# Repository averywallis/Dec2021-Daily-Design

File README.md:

# Dec2021-Daily-Design
 Advent of PCBs 2021

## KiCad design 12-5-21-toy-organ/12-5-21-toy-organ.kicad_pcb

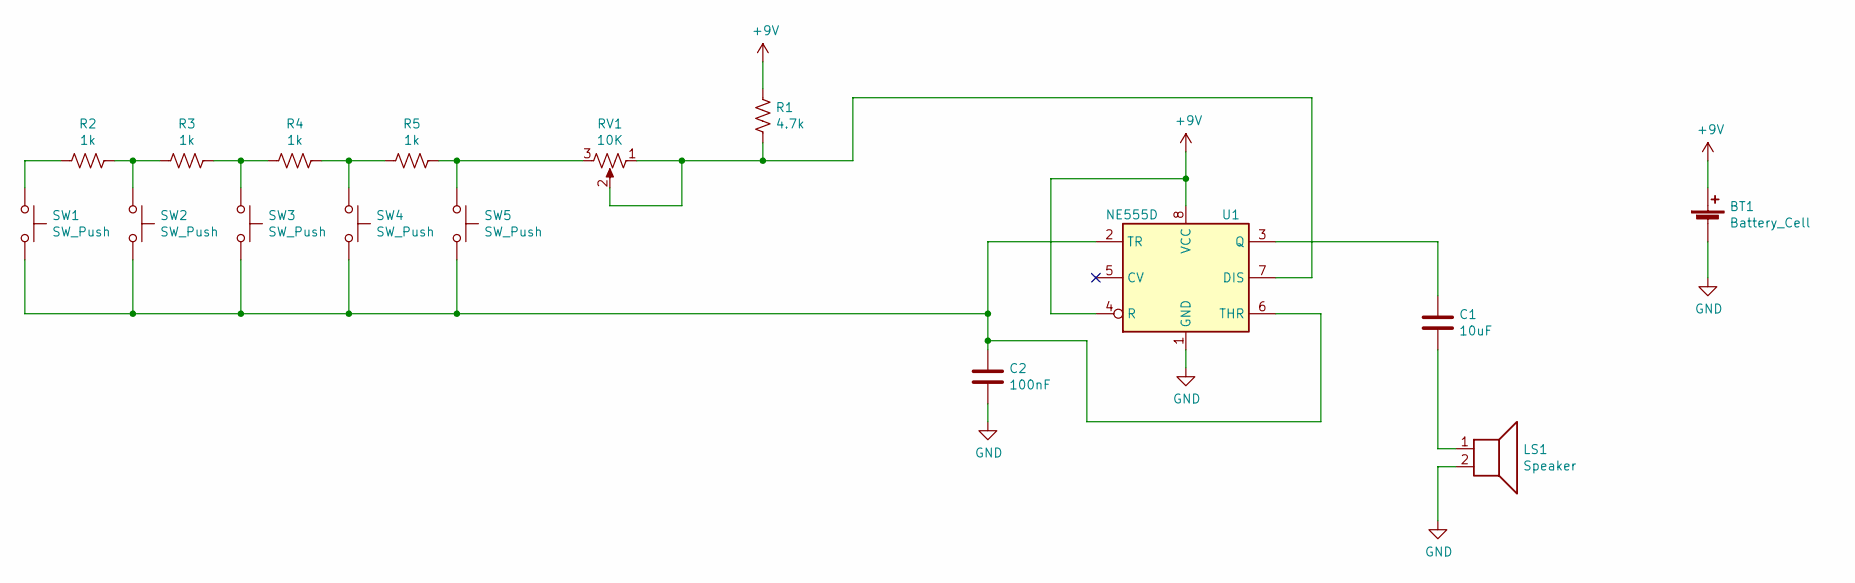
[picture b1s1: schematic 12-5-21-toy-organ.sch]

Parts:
BT1: Battery_Cell; BatteryHolder_Eagle_12BH611-GR
C1: 10uF; C_0805_2012Metric_Pad1.18x1.45mm_HandSolder
C2: 100nF; C_0805_2012Metric_Pad1.18x1.45mm_HandSolder
LS1: Speaker; PinHeader_1x02_P2.54mm_Vertical
R1: 4.7k; R_0805_2012Metric_Pad1.20x1.40mm_HandSolder
R2, R3, R4, R5: 1k; R_0805_2012Metric_Pad1.20x1.40mm_HandSolder
RV1: 10K; Potentiometer_Bourns_3299W_Vertical
SW1, SW2, SW3, SW4, SW5: SW_Push; SW_SPST_CK_RS282G05A3
U1: NE555D; SOIC-8_3.9x4.9mm_P1.27mm

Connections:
+9V: BT1.1 (+), R1.2, U1.4 (R), U1.8 (VCC)
GND: BT1.2 (-), C2.2, LS1.2, U1.1 (GND)
unnamed: C1.1, U1.3 (Q)
unnamed: C1.2, LS1.1
unnamed: C2.1, SW1.2, SW2.2, SW3.2, SW4.2, SW5.2, U1.2 (TR), U1.6 (THR)
unnamed: R1.1, RV1.1, RV1.2, U1.7 (DIS)
unnamed: R2.1, SW1.1
unnamed: R2.2, R3.1, SW2.1
unnamed: R3.2, R4.1, SW3.1
unnamed: R4.2, R5.1, SW4.1
unnamed: R5.2, RV1.3, SW5.1

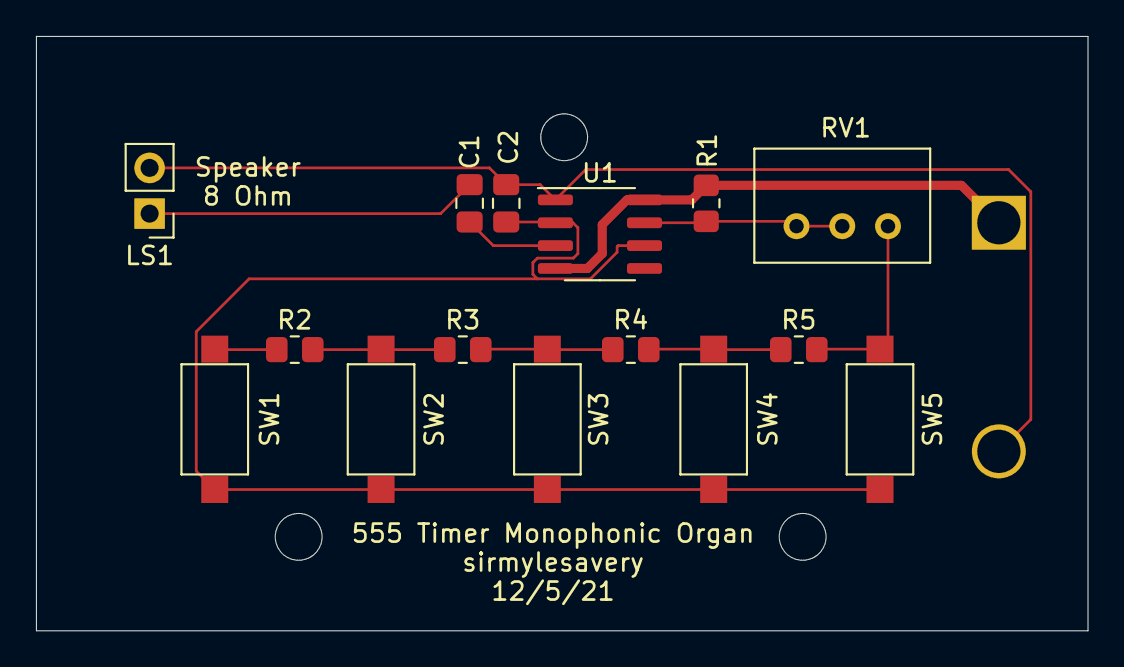
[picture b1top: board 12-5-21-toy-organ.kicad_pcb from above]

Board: 2 copper layers, 58.4 x 33.0 mm, 16 parts (1 on the bottom side), 11 nets.

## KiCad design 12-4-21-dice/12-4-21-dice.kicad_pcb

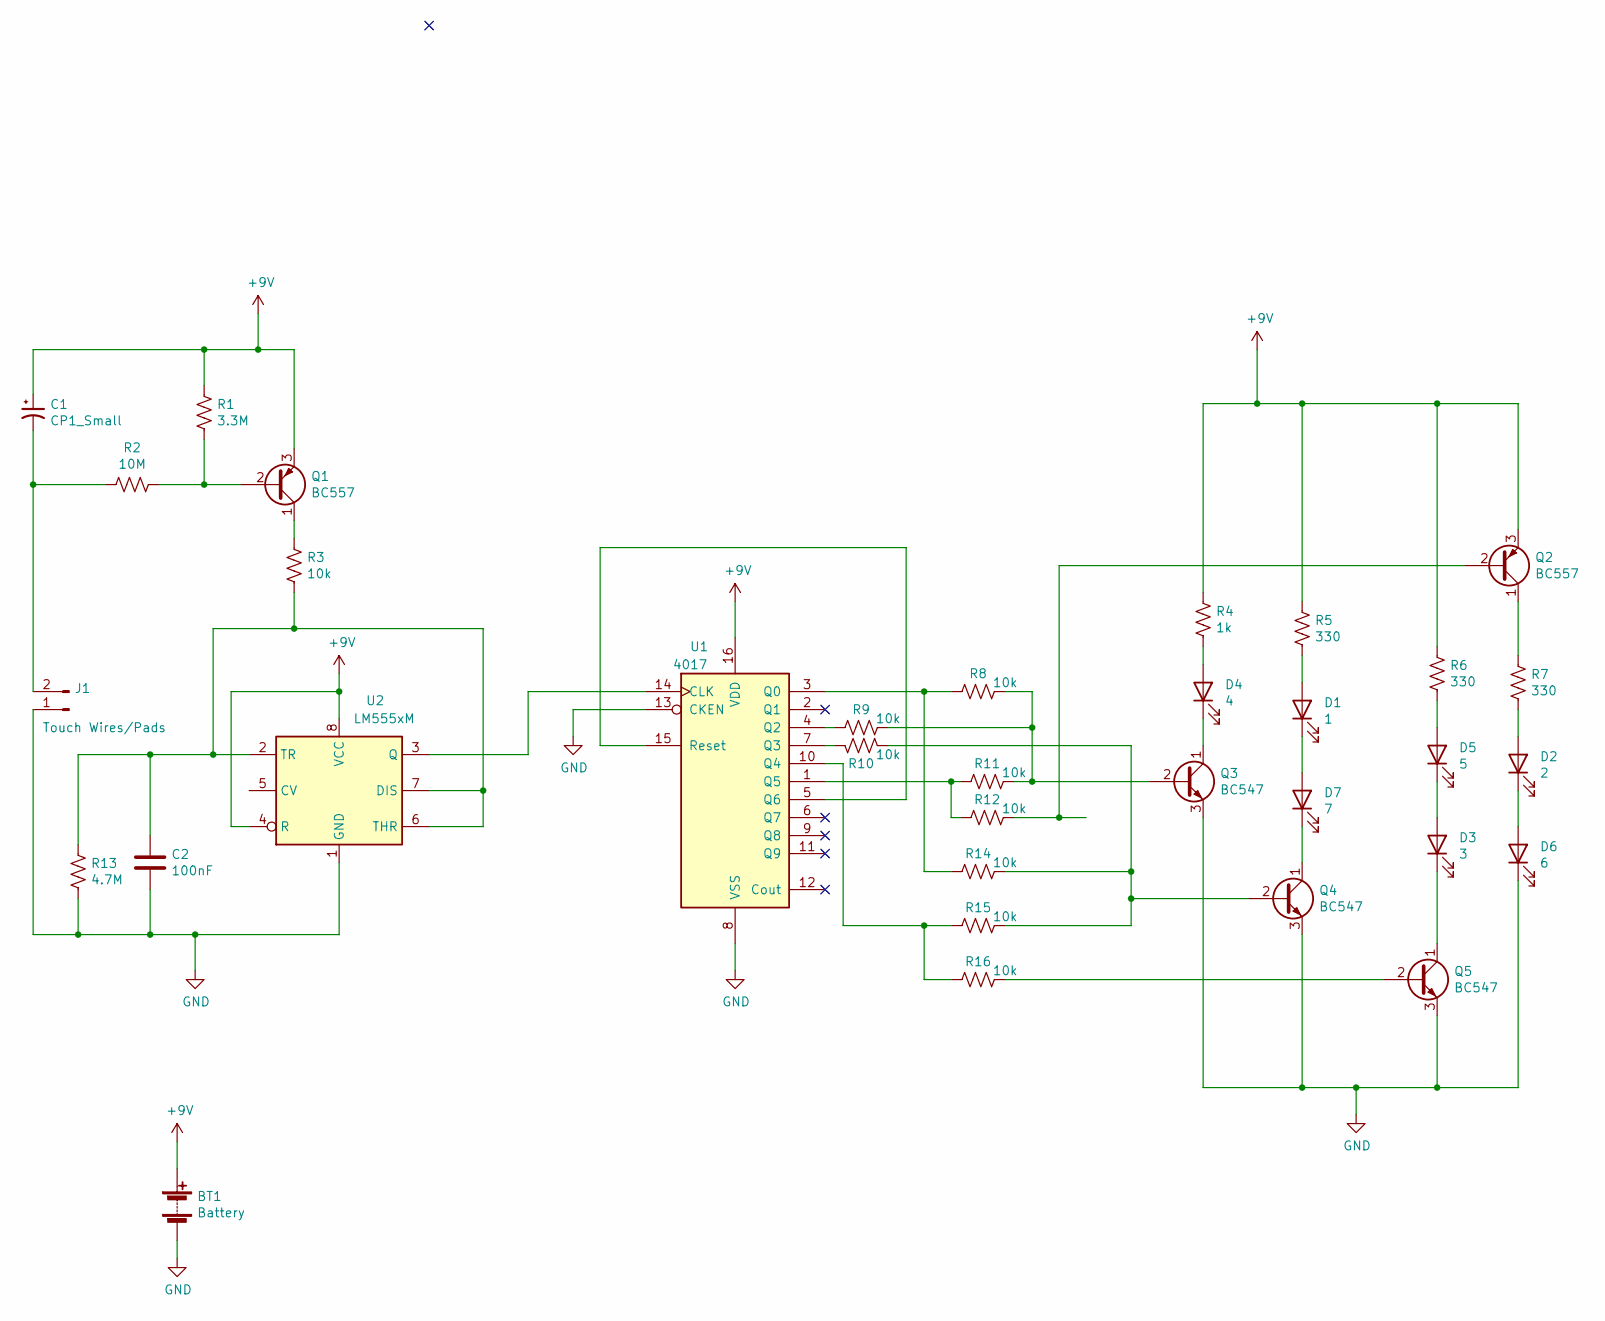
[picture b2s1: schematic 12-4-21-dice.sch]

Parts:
BT1: Battery; BatteryHolder_Eagle_12BH611-GR
C1: CP1_Small; CP_Radial_D5.0mm_P2.50mm
C2: 100nF; C_0805_2012Metric_Pad1.18x1.45mm_HandSolder
D1: 1; LED_0805_2012Metric_Pad1.15x1.40mm_HandSolder
D2: 2; LED_0805_2012Metric_Pad1.15x1.40mm_HandSolder
D3: 3; LED_0805_2012Metric_Pad1.15x1.40mm_HandSolder
D4: 4; LED_0805_2012Metric_Pad1.15x1.40mm_HandSolder
D5: 5; LED_0805_2012Metric_Pad1.15x1.40mm_HandSolder
D6: 6; LED_0805_2012Metric_Pad1.15x1.40mm_HandSolder
D7: 7; LED_0805_2012Metric_Pad1.15x1.40mm_HandSolder
J1: Touch Wires/Pads; C_3640_9110Metric_Pad2.10x10.45mm_HandSolder
Q1, Q2: BC557; TO-92_Inline
Q3, Q4, Q5: BC547; TO-92_Inline
R1: 3.3M; R_0805_2012Metric_Pad1.20x1.40mm_HandSolder
R2: 10M; R_0805_2012Metric_Pad1.20x1.40mm_HandSolder
R3, R8, R9, R10, R11, R12, R14, R15, R16: 10k; R_0805_2012Metric_Pad1.20x1.40mm_HandSolder
R4: 1k; R_0805_2012Metric_Pad1.20x1.40mm_HandSolder
R5, R6, R7: 330; R_0805_2012Metric_Pad1.20x1.40mm_HandSolder
R13: 4.7M; R_0805_2012Metric_Pad1.20x1.40mm_HandSolder
U1: 4017; DIP-16_W10.16mm
U2: LM555xM; SOIC-8_3.9x4.9mm_P1.27mm

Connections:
+9V: BT1.1 (+), C1.1, Q1.3 (E), Q2.3 (E), R1.1, R4.1, R5.1, R6.1, U1.16 (VDD), U2.4 (R), U2.8 (VCC)
GND: BT1.2 (-), C2.2, D6.1 (K), J1.1, Q3.3 (E), Q4.3 (E), Q5.3 (E), R13.2, U1.8 (VSS), U1.13 (CKEN), U2.1 (GND)
unnamed: C1.2, J1.2, R2.2
unnamed: C2.1, R3.2, R13.1, U2.2 (TR), U2.6 (THR), U2.7 (DIS)
unnamed: D1.1 (K), D7.2 (A)
unnamed: D1.2 (A), R5.2
unnamed: D2.1 (K), D6.2 (A)
unnamed: D2.2 (A), R7.2
unnamed: D3.1 (K), Q5.1 (C)
unnamed: D3.2 (A), D5.1 (K)
unnamed: D4.1 (K), Q3.1 (C)
unnamed: D4.2 (A), R4.2
unnamed: D5.2 (A), R6.2
unnamed: D7.1 (K), Q4.1 (C)
unnamed: Q1.1 (C), R3.1
unnamed: Q1.2 (B), R1.2, R2.1
unnamed: Q2.1 (C), R7.1
unnamed: Q2.2 (B), R12.1
unnamed: Q3.2 (B), R8.1, R9.1, R11.1
unnamed: Q4.2 (B), R10.1, R14.1, R15.1
unnamed: Q5.2 (B), R16.1
unnamed: R9.2, U1.4 (Q2)
unnamed: R10.2, U1.7 (Q3)
unnamed: R11.2, R12.2, U1.1 (Q5)
unnamed: R8.2, R14.2, U1.3 (Q0)
unnamed: R15.2, R16.2, U1.10 (Q4)
unnamed: U1.14 (CLK), U2.3 (Q)
unnamed: U1.5 (Q6), U1.15 (Reset)

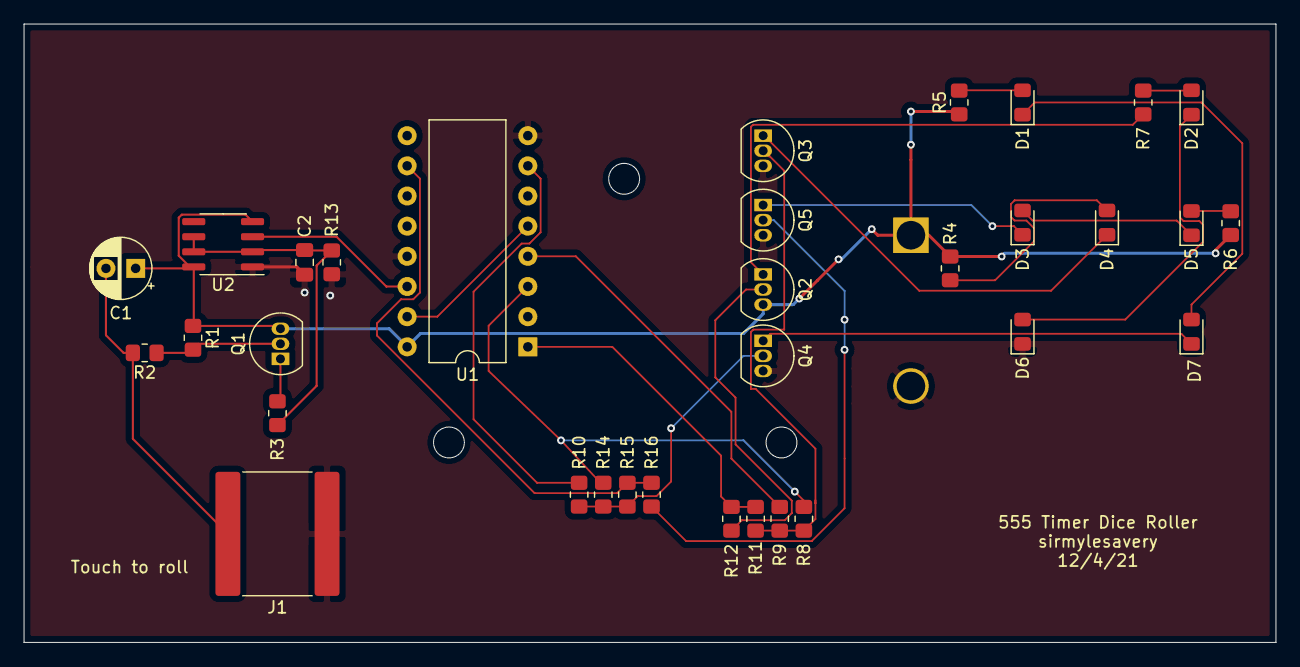
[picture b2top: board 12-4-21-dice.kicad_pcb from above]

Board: 2 copper layers, 105.4 x 52.1 mm, 34 parts (1 on the bottom side), 28 nets.

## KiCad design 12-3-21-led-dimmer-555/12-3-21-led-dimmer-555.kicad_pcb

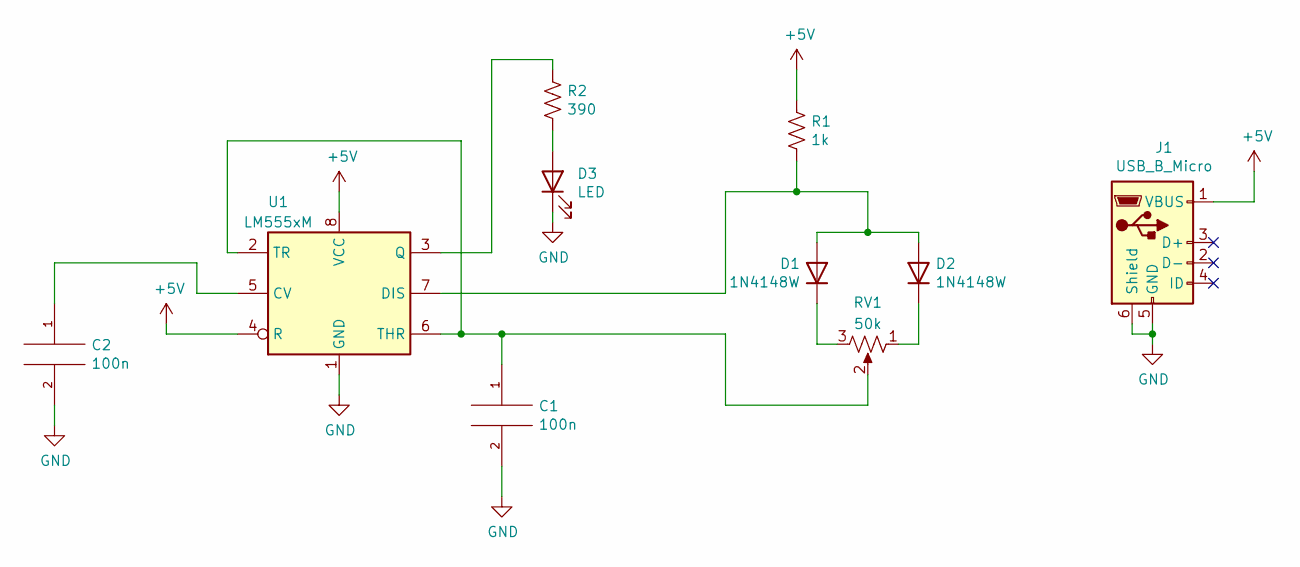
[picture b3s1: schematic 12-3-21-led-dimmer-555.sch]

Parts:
C1, C2: 100n; C_0603_1608Metric
D1, D2: 1N4148W; D_SOD-123
D3: LED; LED_0603_1608Metric
J1: USB_B_Micro; USB_Micro-B_Amphenol_10103594-0001LF_Horizontal
R1: 1k; R_0603_1608Metric
R2: 390; R_0603_1608Metric
RV1: 50k; Potentiometer_Bourns_3224G_Horizontal
U1: LM555xM; SOIC-8_3.9x4.9mm_P1.27mm

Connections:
+5V: J1.1 (VBUS), R1.1, U1.4 (R), U1.8 (VCC)
GND: C1.2, C2.2, D3.1 (K), J1.5 (GND), J1.6 (Shield), U1.1 (GND)
unnamed: C1.1, RV1.2, U1.2 (TR), U1.6 (THR)
unnamed: C2.1, U1.5 (CV)
unnamed: D1.1 (K), RV1.3
unnamed: D1.2 (A), D2.2 (A), R1.2, U1.7 (DIS)
unnamed: D2.1 (K), RV1.1
unnamed: D3.2 (A), R2.2
unnamed: R2.1, U1.3 (Q)

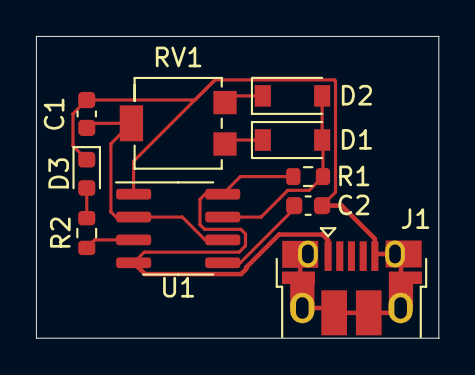
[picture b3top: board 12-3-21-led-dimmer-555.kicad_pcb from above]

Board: 2 copper layers, 22.4 x 16.8 mm, 10 parts (0 on the bottom side), 9 nets.

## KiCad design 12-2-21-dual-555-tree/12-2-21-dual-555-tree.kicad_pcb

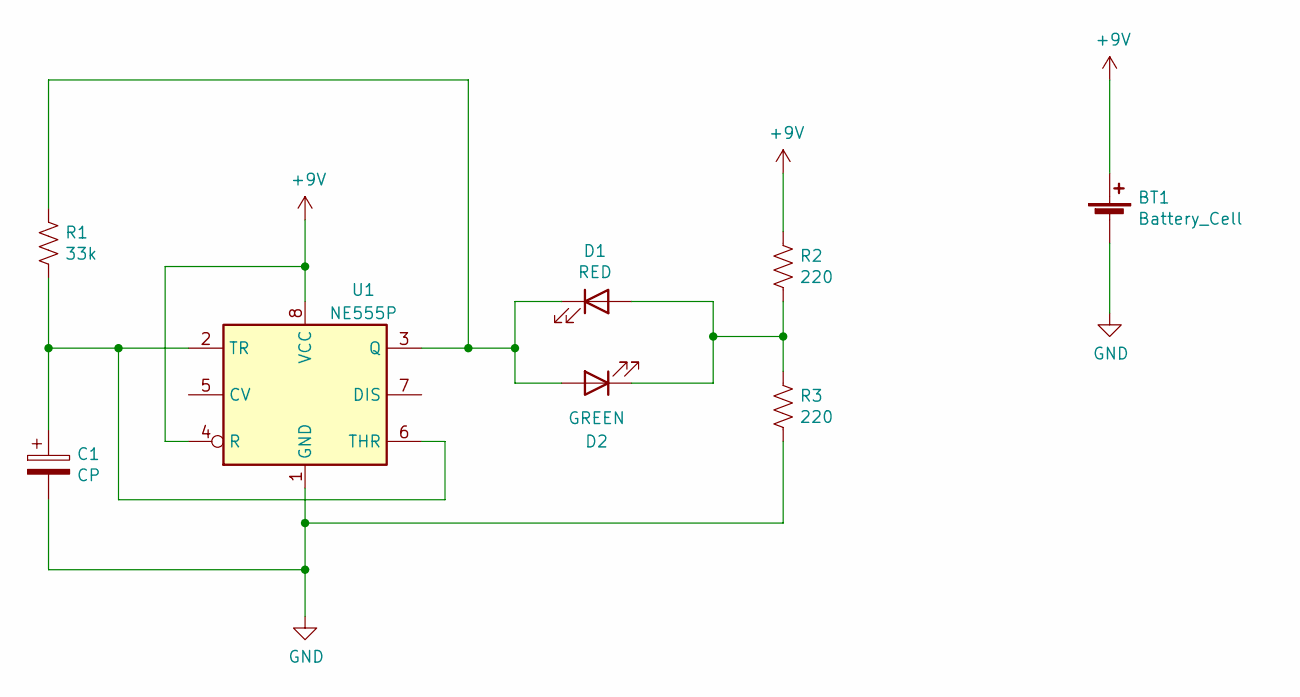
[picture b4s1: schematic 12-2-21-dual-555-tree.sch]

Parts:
BT1: Battery_Cell; BatteryHolder_Eagle_12BH611-GR
C1: CP; CP_Radial_D5.0mm_P2.50mm
D1: RED; LED_0805_2012Metric_Pad1.15x1.40mm_HandSolder
D2: GREEN; LED_0805_2012Metric_Pad1.15x1.40mm_HandSolder
R1: 33k; R_0805_2012Metric_Pad1.20x1.40mm_HandSolder
R2, R3: 220; R_0805_2012Metric_Pad1.20x1.40mm_HandSolder
U1: NE555P; DIP-8_W7.62mm

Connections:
+9V: BT1.1 (+), R2.1, U1.4 (R), U1.8 (VCC)
GND: BT1.2 (-), C1.2, R3.2, U1.1 (GND)
unnamed: C1.1, R1.2, U1.2 (TR), U1.6 (THR)
unnamed: D1.1 (K), D2.2 (A), R1.1, U1.3 (Q)
unnamed: D1.2 (A), D2.1 (K), R2.2, R3.1

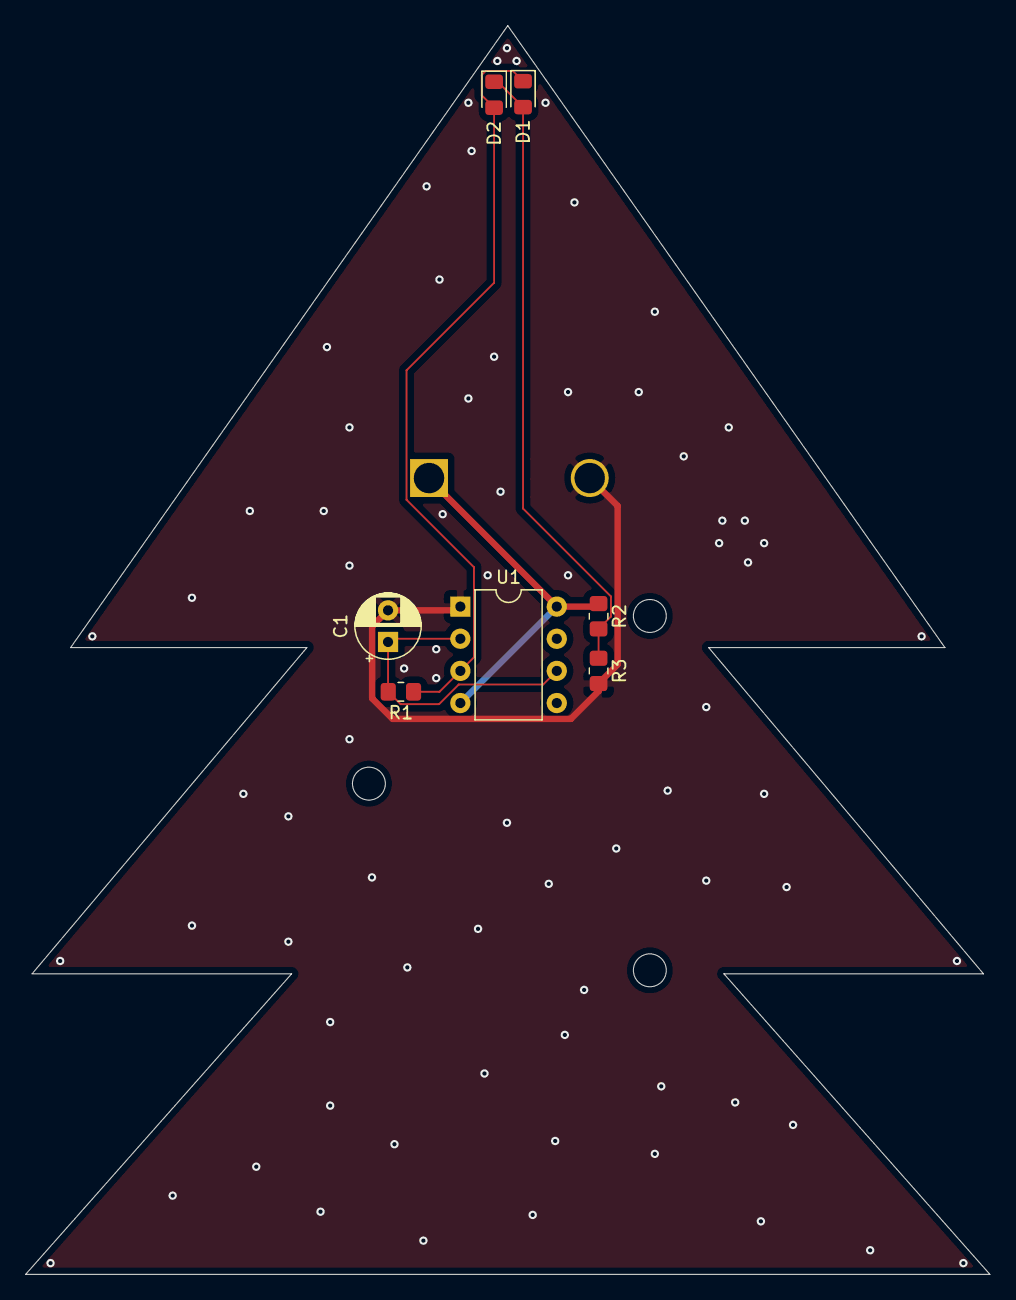
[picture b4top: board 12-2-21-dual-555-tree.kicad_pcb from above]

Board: 2 copper layers, 76.2 x 98.7 mm, 8 parts (1 on the bottom side), 5 nets.

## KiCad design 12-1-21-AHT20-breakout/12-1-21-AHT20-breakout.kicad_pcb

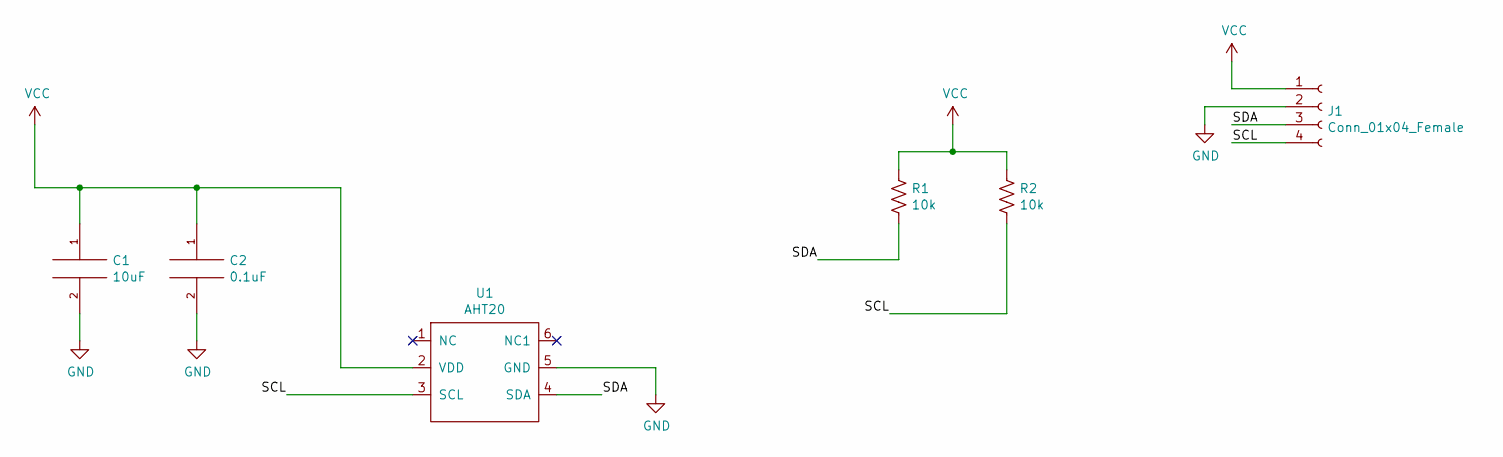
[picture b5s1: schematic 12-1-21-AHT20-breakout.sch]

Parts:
C1: 10uF; C_0805_2012Metric_Pad1.18x1.45mm_HandSolder
C2: 0.1uF; C_0805_2012Metric_Pad1.18x1.45mm_HandSolder
J1: Conn_01x04_Female; PinHeader_1x04_P2.54mm_Vertical
R1, R2: 10k; R_0805_2012Metric_Pad1.20x1.40mm_HandSolder
U1: AHT20

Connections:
/SCL: J1.4, R2.1, U1.3 (SCL)
/SDA: J1.3, R1.1, U1.4 (SDA)
GND: C1.2, C2.2, J1.2, U1.5 (GND)
VCC: C1.1, C2.1, J1.1, R1.2, R2.2, U1.2 (VDD)

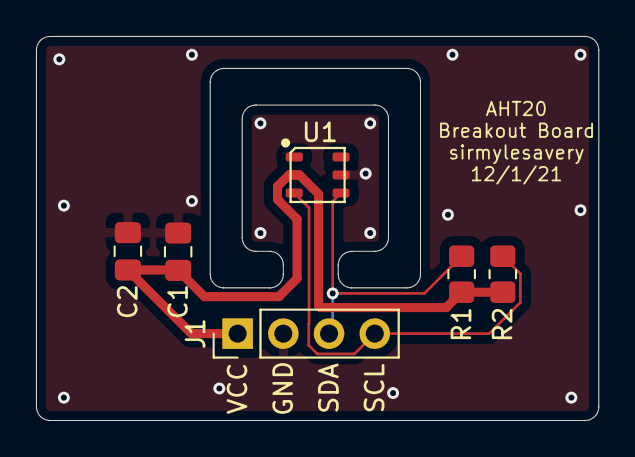
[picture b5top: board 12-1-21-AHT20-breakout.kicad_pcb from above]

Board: 2 copper layers, 31.2 x 21.3 mm, 6 parts (0 on the bottom side), 4 nets.

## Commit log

2021-12-02 AHT20 Breakout
    Breakout board for AHT20 temperature and humidity sensor. Attempt at advent of PCBs for 2021
2021-12-03 12/2/21 Design
    Basic 555 timer that driver 2 LEDs at the top of a PCB tree
2021-12-03 12/3/21 Design
    A simple 555 timer LED dimmer
2021-12-05 12/4/21 design
    A 555 timer dice roller
2021-12-05 12/5/21 Daily Design
    A basic 555 timer driven monophonic organ
